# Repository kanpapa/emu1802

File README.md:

# emu1802
The computer with only COSMAC CDP1802 and PIC18F47Q43/PIC18F27Q43  
developed by Kazuhiro Ouchi

The purpose of this experiment is to see if it is possible to make a real COSMAC work with fewer components, at a lower cost, and more compactly.

The EMU1802 is replacement the CPU of the EMUZ80 with a COSMAC.  
The EMU1802-mini is replacement the PIC of the EMU1802 with a PIC18F27Q43.  

## Repository Contents
- [emu1802.X](/emu1802.X/) - PIC18F47Q43 ROM RAM and UART emulation firmware for EMU1802
- [emu1802mini.X](/emu1802mini.X/) - PIC18F27Q43 ROM RAM and UART emulation firmware for EMU1802-mini
- [production](/production/) - Firmware hex files for EMU1802-mini
- [idiotmon](/idiotmon/) - IDIOT/4 monitor and sample programs
- [kicad/emu1802_sch.pdf](/kicad/emu1802_sch.pdf) - schematic of EMU1802
- [kicad/emu1802_mini_sch.pdf](/kicad/emu1802_mini_sch.pdf) - schematic of EMU1802-mini
- [kicad/emu1802_mini_bom.md](/kicad/emu1802_mini_bom.md) - BOM of EMU1802-mini
- [test_programs](/test_programs/) - Test programs for EMU1802 hardware
- [tools/bin2hexsrc.py](/tools/bin2hexsrc.py) - A tool to convert binaries to HEX
- [EMU1802mini_Setup_ja.md](/EMU1802mini_Setup_ja.md) - Setup manual for EMU1802mini (Japanese)
- [README.md](/README.md) - This manual

## Development tools
- [Microchip MPLAB IDE v6.00](https://www.microchip.com/en-us/tools-resources/develop/mplab-x-ide)
- [Microchip MPLAB SNAP](https://www.microchip.com/en-us/development-tool/PG164100)
- [SB-Assembler 3](https://www.sbprojects.net/sbasm/)
- Python3

## Blog
You can also refer to my blog. (in Japanese)  
https://kanpapa.com/cosmac/blog/emu1802/

## Pictures

The EMU1802-mini  

Testing of the EMU1802-mini  

The idiot monitor is working on the EMU1802-mini  

Prototype of The EMU1802  

## License Information
References to any products, programs or services do not imply that they will be available in all countries in which their respective owner operates.  

Company, product, or services names may be trademarks or services marks of others.  

All libraries used in this code are copyright their respective authors.  

This project is based on the EMUZ80 hardware and software developed by Tetsuya Suzuki.

EMUZ80 - The computer with only Z80 and PIC18F47Q43  
  Written by Tetsuya Suzuki  
  https://github.com/vintagechips/emuz80  

The firmware includes the IDIOT monitor.  

IDIOT/4 MONITOR FOR THE 1802  
  WRITTEN: 6/23/82 BY LEE HART  
  COPYRIGHT 1982-85 BY TMSI  
  This program may be used for any noncommercial use free of charge.  
  fixes by Herb Johnson HRJ April 2010, Jan 2014  
  https://www.retrotechnology.com/memship/mship_idiot.html

Thanks to Gazelle for optimizing the firmware.  

  Modified by Gazelle  
  https://drive.google.com/drive/folders/14-OX5THzVz1BVxLPXheExVnpIBqS79NJ  
  1st release 2022-7-29

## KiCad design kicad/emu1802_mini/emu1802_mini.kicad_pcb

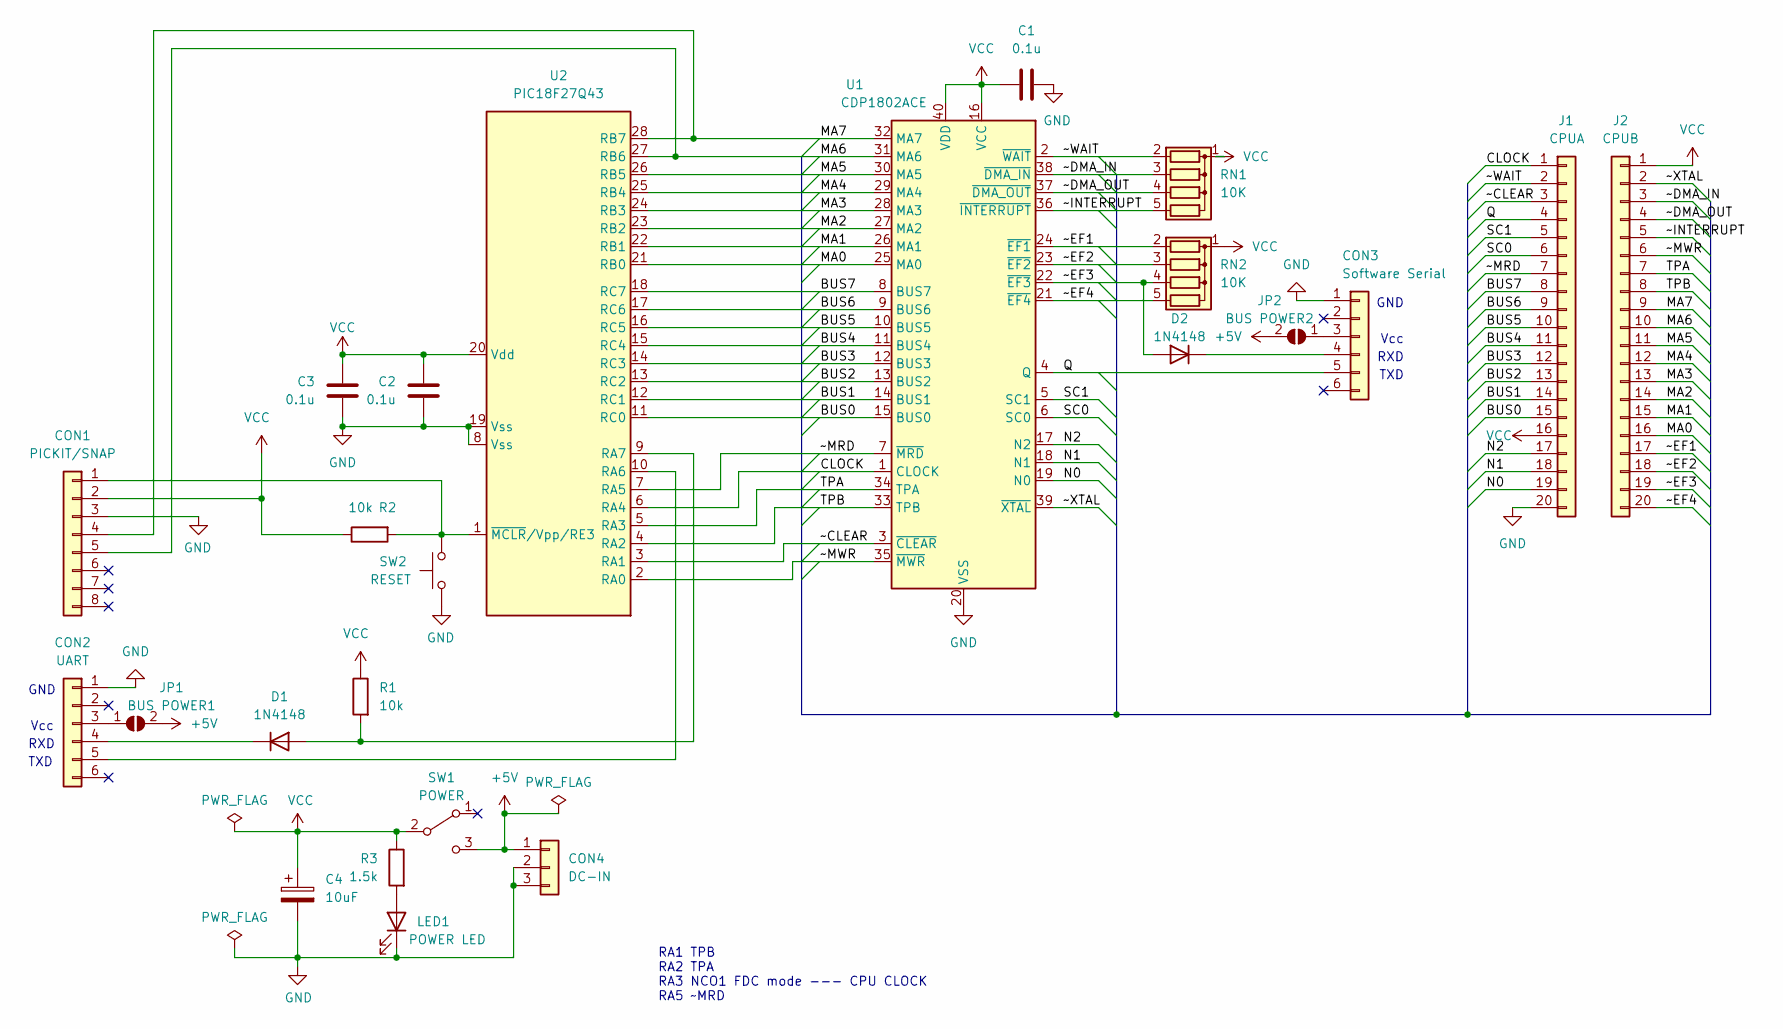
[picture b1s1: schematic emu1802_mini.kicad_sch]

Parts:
C1, C2, C3: 0.1u; C_Disc_D3.0mm_W1.6mm_P2.50mm
C4: 10uF; CP_Radial_D4.0mm_P2.00mm
CON1: PICKIT/SNAP; PinHeader_1x08_P2.54mm_Vertical
CON2: UART; PinHeader_1x06_P2.54mm_Vertical
CON3: Software Serial; PinHeader_1x06_P2.54mm_Vertical
CON4: DC-IN; PinHeader_1x03_P2.54mm_Vertical
D1, D2: 1N4148; D_T-1_P5.08mm_Horizontal
J1: CPUA; PinSocket_1x20_P2.54mm_Vertical
J2: CPUB; PinSocket_1x20_P2.54mm_Vertical
JP1: BUS POWER1; SolderJumper-2_P1.3mm_Open_RoundedPad1.0x1.5mm
JP2: BUS POWER2; SolderJumper-2_P1.3mm_Open_RoundedPad1.0x1.5mm
LED1: POWER LED; LED_D3.0mm
R1, R2: 10k; R_Axial_DIN0204_L3.6mm_D1.6mm_P5.08mm_Horizontal
R3: 1.5k; R_Axial_DIN0204_L3.6mm_D1.6mm_P5.08mm_Horizontal
RN1, RN2: 10K; R_Array_SIP5
SW1: POWER; PinHeader_1x03_P2.54mm_Vertical
SW2: RESET; SW_PUSH_6mm
U1: CDP1802ACE; DIP-40_W15.24mm_Socket
U2: PIC18F27Q43; DIP-28_W7.62mm_Socket

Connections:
+5V: CON4.1, JP1.2 (B), JP2.2 (B), SW1.3 (C)
/BUS0: J1.15, U1.15 (BUS0), U2.11 (RC0)
/BUS1: J1.14, U1.14 (BUS1), U2.12 (RC1)
/BUS2: J1.13, U1.13 (BUS2), U2.13 (RC2)
/BUS3: J1.12, U1.12 (BUS3), U2.14 (RC3)
/BUS4: J1.11, U1.11 (BUS4), U2.15 (RC4)
/BUS5: J1.10, U1.10 (BUS5), U2.16 (RC5)
/BUS6: J1.9, U1.9 (BUS6), U2.17 (RC6)
/BUS7: J1.8, U1.8 (BUS7), U2.18 (RC7)
/CLOCK: J1.1, U1.1 (CLOCK), U2.6 (RA4)
/MA0: J2.16, U1.25 (MA0), U2.21 (RB0)
/MA1: J2.15, U1.26 (MA1), U2.22 (RB1)
/MA2: J2.14, U1.27 (MA2), U2.23 (RB2)
/MA3: J2.13, U1.28 (MA3), U2.24 (RB3)
/MA4: J2.12, U1.29 (MA4), U2.25 (RB4)
/MA5: J2.11, U1.30 (MA5), U2.26 (RB5)
/MA6: CON1.5, J2.10, U1.31 (MA6), U2.27 (RB6)
/MA7: CON1.4, J2.9, U1.32 (MA7), U2.28 (RB7)
/N0: J1.19, U1.19 (N0)
/N1: J1.18, U1.18 (N1)
/N2: J1.17, U1.17 (N2)
/Q: CON3.5, J1.4, U1.4 (Q)
/SC0: J1.6, U1.6 (SC0)
/SC1: J1.5, U1.5 (SC1)
/TPA: J2.7, U1.34 (TPA), U2.5 (RA3)
/TPB: J2.8, U1.33 (TPB), U2.4 (RA2)
/~CLEAR: J1.3, U1.3 (~CLEAR), U2.3 (RA1)
/~DMA_IN: J2.3, RN1.3 (R2), U1.38 (~DMA_IN)
/~DMA_OUT: J2.4, RN1.4 (R3), U1.37 (~DMA_OUT)
/~EF1: J2.17, RN2.2 (R1), U1.24 (~EF1)
/~EF2: J2.18, RN2.3 (R2), U1.23 (~EF2)
/~EF3: D2.2 (A), J2.19, RN2.4 (R3), U1.22 (~EF3)
/~EF4: J2.20, RN2.5 (R4), U1.21 (~EF4)
/~INTERRUPT: J2.5, RN1.5 (R4), U1.36 (~INTERRUPT)
/~MRD: J1.7, U1.7 (~MRD), U2.7 (RA5)
/~MWR: J2.6, U1.35 (~MWR), U2.2 (RA0)
/~WAIT: J1.2, RN1.2 (R1), U1.2 (~WAIT)
/~XTAL: J2.2, U1.39 (~XTAL)
GND: C1.1, C2.2, C3.2, C4.2, CON1.3, CON2.1, CON3.1, CON4.2, CON4.3, J1.20, LED1.1 (K), SW2.2, U1.20 (VSS), U2.8 (Vss), U2.19 (Vss)
unnamed: CON1.1, R2.2, SW2.1, U2.1 (~MCLR/Vpp/RE3)
unnamed: CON2.3, JP1.1 (A)
unnamed: CON2.4, D1.1 (K)
unnamed: CON2.5, U2.10 (RA6)
unnamed: CON3.3, JP2.1 (A)
unnamed: CON3.4, D2.1 (K)
unnamed: D1.2 (A), R1.2, U2.9 (RA7)
unnamed: LED1.2 (A), R3.2
VCC: C1.2, C2.1, C3.1, C4.1, CON1.2, J1.16, J2.1, R1.1, R2.1, R3.1, RN1.1 (common), RN2.1 (common), SW1.2 (B), U1.16 (VCC), U1.40 (VDD), U2.20 (Vdd)

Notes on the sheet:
RXD
TXD
GND
Vcc
RA1 TPB RA2 TPA RA3 NCO1 FDC mode --- CPU CLOCK RA5 ~MRD

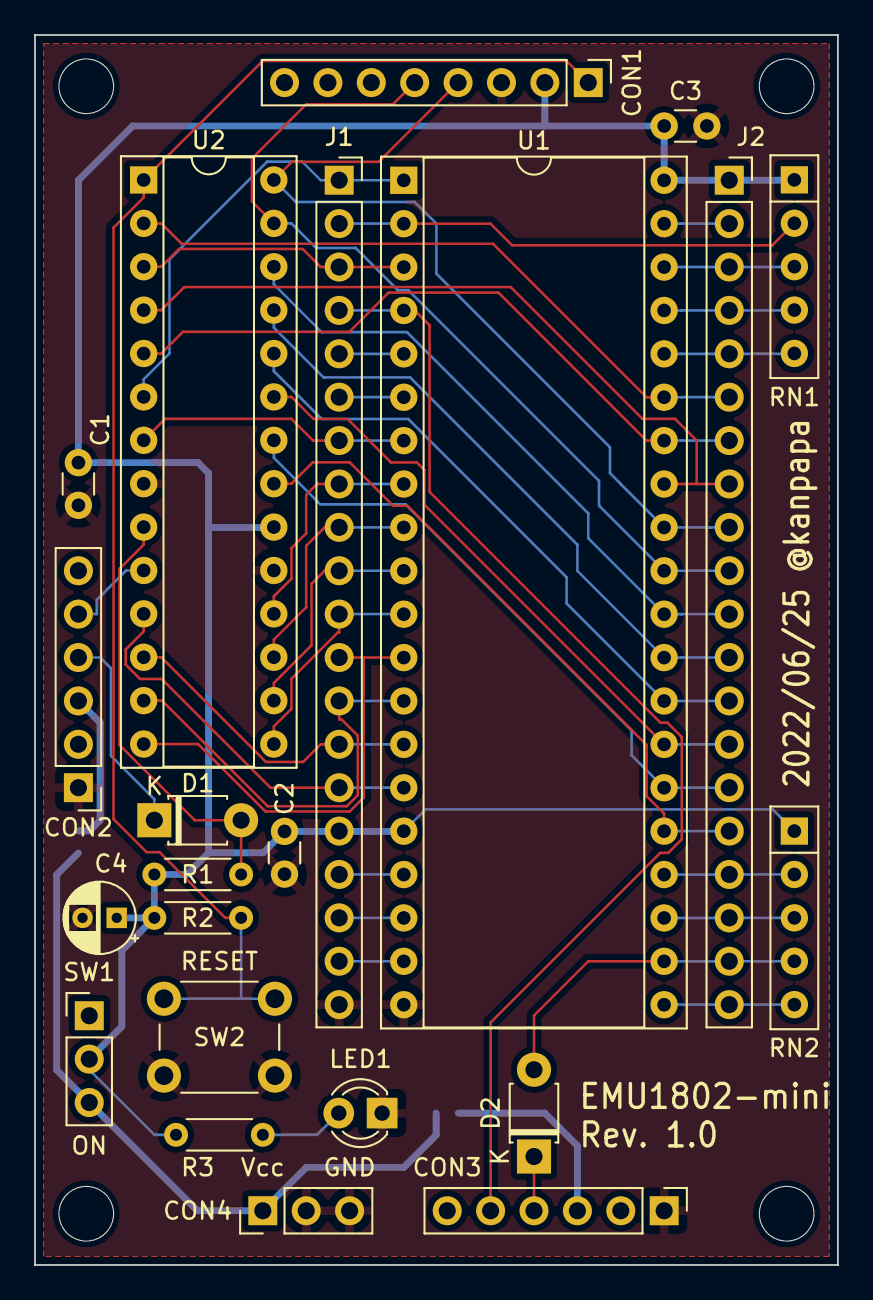
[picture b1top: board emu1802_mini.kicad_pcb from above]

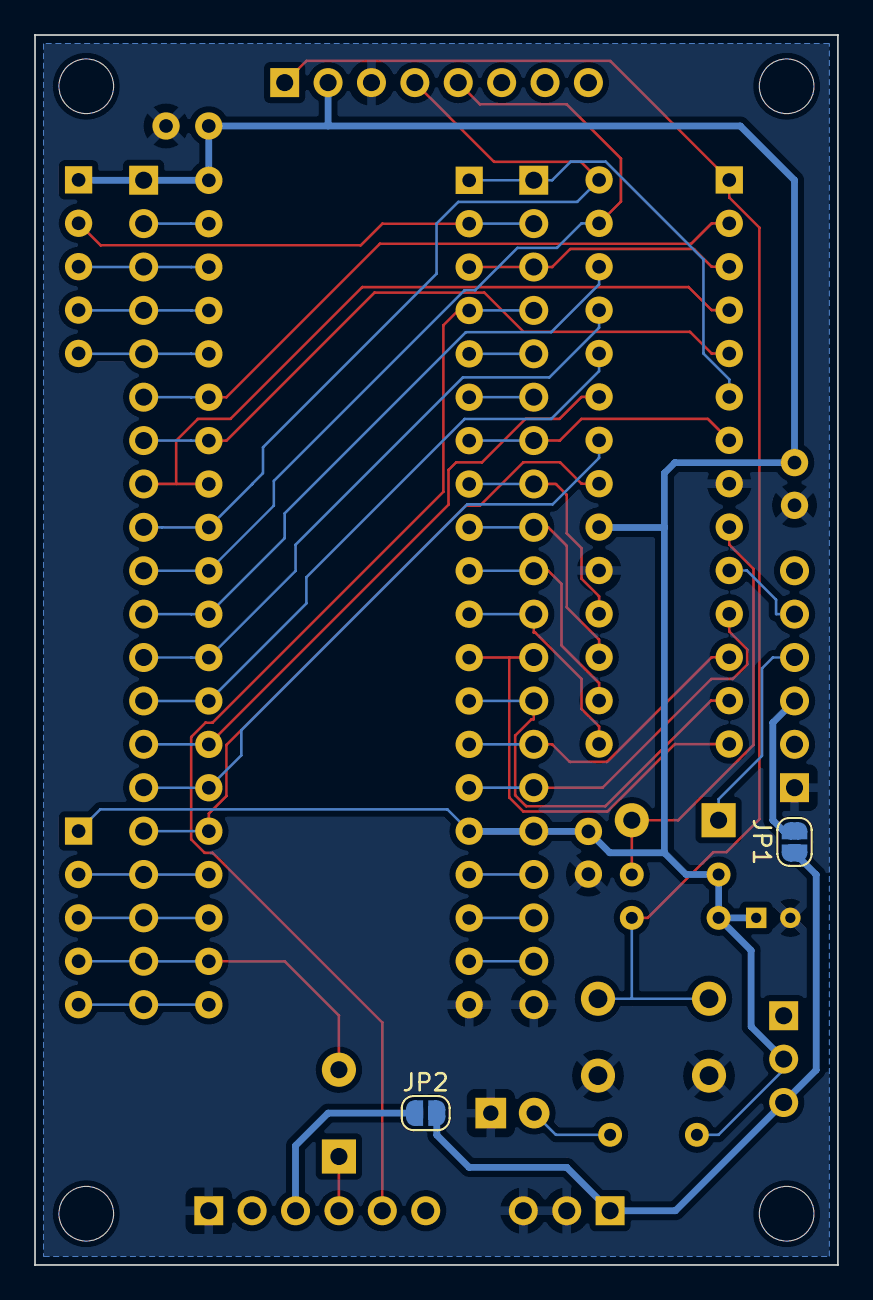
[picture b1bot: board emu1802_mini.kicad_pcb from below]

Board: 2 copper layers, 47.0 x 72.0 mm, 28 parts (2 on the bottom side), 48 nets.

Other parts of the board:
MH1, MH2, MH3, MH4: MountingHole_3.2mm_M3

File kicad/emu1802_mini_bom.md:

# EMU1802-mini Rev1.0 BOM
|Item|Qty|Reference(s)|Value|Description|Datasheet|
| --- | --- | --- | --- | --- | --- |
|1|3|C1, C2, C3|0.1u|Leaded MLCC 0.1uF50V 2.54mm|https://akizukidenshi.com/catalog/g/gP-00090/|
|2|1|C4|10uF|capacitor 10uF50V|https://akizukidenshi.com/catalog/g/gP-03116/|
|3|1|CON1|PICKIT/SNAP|2.54mm 8-Pin header strip straight(or right angle) single row|https://akizukidenshi.com/catalog/g/gC-00167/|
|4|1|CON2|UART|2.54mm 6-Pin header strip straight(or right angle) single row|https://akizukidenshi.com/catalog/g/gC-00167/|
|5|1|CON3|Software Serial|2.54mm 6-Pin header strip straight(or right angle) single row|https://akizukidenshi.com/catalog/g/gC-00167/|
|6|1|CON4|DC-IN|2.54mm 3-Pin header strip straight(or right angle) single row|https://akizukidenshi.com/catalog/g/gC-00167/|
|7|2|D1, D2|1N4148| Small Signal Diode 1N4148|https://akizukidenshi.com/catalog/g/gI-00941/|
|8|2|J1, J2|CPUA/B|2.54mm 20-Pin female header single row straight dip|https://akizukidenshi.com/catalog/g/gC-03077/|
|9|1|LED1|POWER LED|3mm LED|https://akizukidenshi.com/catalog/g/gI-11577/|
|10|2|R1, R2|10k|resistor 10k 1/6W|https://akizukidenshi.com/catalog/g/gR-16103/|
|11|1|R3|1.5k|resistor 1.5k 1/6W|https://akizukidenshi.com/catalog/g/gR-16152/|
|12|2|RN1,RN2|10K|SIP resistor 5-pin 4 x 10k|https://akizukidenshi.com/catalog/g/gR-11909/|
|13|1|SW1|POWER|slide switch SS-12D00G3|https://akizukidenshi.com/catalog/g/gP-15707/|
|14|1|SW2|RESET|tact switch TS-0606|https://akizukidenshi.com/catalog/g/gP-03649/|
|15|1|U1|CDP1802ACE|CDP1802ACE microprocessor|http://www.cosmacelf.com/publications/data-sheets/cdp1802.pdf|
|16|1|U2|PIC18F27Q43|Microchip PIC18F27Q43 microprocessor|https://akizukidenshi.com/catalog/g/gI-16593/|
|17|1|U1 socket||40-Pin IC socket 600mil |https://akizukidenshi.com/catalog/g/gP-00034/|
|18|1|U2 socket||28-Pin IC socket 300mil|https://akizukidenshi.com/catalog/g/gP-01339/|

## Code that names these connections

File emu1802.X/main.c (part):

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#pragma config FCMEN = ON       // Fail-Safe Clock Monitor Enable bit (Fail-Safe Clock Monitor enabled)

// CONFIG3
#pragma config MCLRE = EXTMCLR  // MCLR Enable bit (If LVP = 0, MCLR pin is MCLR; If LVP = 1, RE3 pin function is MCLR )
#pragma config PWRTS = PWRT_OFF // Power-up timer selection bits (PWRT is disabled)
#pragma config MVECEN = ON      // Multi-vector enable bit (Multi-vector enabled, Vector table used for interrupts)
#pragma config IVT1WAY = ON     // IVTLOCK bit One-way set enable bit (IVTLOCKED bit can be cleared and set only once)
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    address.h = PORTB;  // Read address high
}

void __interrupt(irq(IOC),base(8)) PIN_MANAGER_IOC()
{   
	// interrupt on change for pin IOCAF1
    if(IOCAFbits.IOCAF1 == 1)
    {
        IOCAF1_ISR();  
    }	
	// interrupt on change for pin IOCAF2
    if(IOCAFbits.IOCAF2 == 1)
    {
        IOCAF2_ISR();  
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
// Called at COSMAC TPB falling edge (PIC18F47Q43 issues WAIT)
void __interrupt(irq(CLC1),base(8)) CLC1_ISR(){
    CLC1IF = 0; // Clear interrupt flag
    
    //address.h = 0; // Read address high (256byte only)
    address.l = PORTB; // Read address low
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// Called at COSMAC TPA falling edge (PIC18F47Q43 issues WAIT)
void __interrupt(irq(CLC2),base(8)) CLC2_ISR()
{
    CLC2IF = 0;         // Clear the CLC interrupt flag
    address.h = PORTB;  // Read address high
}

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
//  Called at COSMAC TPB(RA1) Falling edge
void __interrupt(irq(INT0),base(8)) INT0_ISR(){
    INT0IF = 0; // Clear interrupt flag
    db_setin(); // Set data bus as input
}

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    WPUD = 0xff; // Week pull up
    TRISD = 0xff; // Set as input

    // Address bus A7-A0 pin (RB0-RB7)
    ANSELB = 0x00; // Disable analog function
    WPUB = 0xff; // Week pull up
    TRISB = 0xff; // Set as input

    // Data bus D7-D0 pin (RC0-RC7)
    ANSELC = 0x00; // Disable analog function
    WPUC = 0xff; // Week pull up
    TRISC = 0xff; // Set as input(default)

    // MWR input pin (RE0)
    ANSELE0 = 0; // Disable analog function
    WPUE0 = 1; // Week pull up
    TRISE0 = 1; // Set as input
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
    // INT output pin (RE2) --- Unused
    //ANSELE2 = 0; // Disable analog function
    //LATE2 = 1; // No interrupt request
    //TRISE2 = 0; // Set as output

    // MRD input pin (RA5)
    ANSELA5 = 0; // Disable analog function
    WPUA5 = 1; // Week pull up
    TRISA5 = 1; // Set as intput
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    //U3ON = 1; // Serial port enable
    
    
    // TPB(RA1) CLC1 input pin
    ANSELA1 = 0; // Disable analog function
    WPUA1 = 1; // Week pull up
    TRISA1 = 1; // Set as input
    //CLCIN0PPS = 0x1; //RA1->CLC1:CLCIN0;

    // TPA(RA2) CLC2 input pin
    ANSELA2 = 0; // Disable analog function
    WPUA2 = 1; // Week pull up
    TRISA2 = 1; // Set as input
    //CLCIN1PPS = 0x2; //RA2->CLC1:CLCIN1;

    // RA4 CLC1 output pin --- debug
    //ANSELA4 = 0; // Disable analog function
    //LATA4 = 1; // Default level
    //TRISA4 = 0; // Set as output
    //RA4PPS = 0x01;  //RA4->CLC1:CLC1;

    // RA0 CLC2 output pin --- debug   
    //ANSELA0 = 0; // Disable analog function
    //LATA0 = 1; // Default level
    //TRISA0 = 0; // Set as output
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
    // CLC data inputs select
    CLCnSEL0 = 0x2a;  // D-FF CLK assign NC01
    CLCnSEL1 = 0; // D-FF D assign CLCIN0PPS(RA1) 
    CLCnSEL2 = 127; // D-FF S assign none
    CLCnSEL3 = 127; // D-FF R assign none

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    // INTERRUPT_Initialize
    //
    // Vectored Interrupt Controller setting sequence
    INTCON0bits.IPEN = 1; // Interrupt priority enable

    IVTLOCK = 0x55;
    IVTLOCK = 0xAA;
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
#ifdef false
    // CLC VI enable
    CLC1IF = 0; // Clear the CLC interrupt flag
    CLC1IE = 1; // Enabling CLC1 interrupt
    
    // Assign peripheral interrupt priority vectors
    IPR6bits.CLC2IP = 1;
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    CLCDATA = 0x00;     // CLC2OUT 0; 
    CLCnCON = 0x8C;     // EN enabled; INTN enabled; INTP disabled; MODE 1-input D flip-flop with S and R;

    CLC2IF = 0; // Clear the CLC interrupt flag
    CLC2IE = 1; // Enabling CLC2 interrupt.

#endif

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    INT0IE = 1;
   
    // COSMAC start
    GIE = 1; // Global interrupt enable
    LATE1 = 1; // Release reset COSMAC ~CLEAR(RE1)
    
    while(1); // All things come to those who wait
}
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
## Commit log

2022-06-05 1st commit
2022-06-05 Added schematic of EMU1802.
2022-06-05 Fixed CON2 and CON3
2022-06-05 Added sample programs for IDIOT monitor
2022-06-19 Added EMU1802-mini Schematic
2022-06-19 Added emu1802mini Project
2022-06-20 Added BOM for EMU1802-mini
2022-06-20 Updated BOM
2022-06-22 Added IDIOT/4 Monitor
2022-06-22 Added test programs
2022-06-22 Added setup manual for EMU1802mini
2022-06-22 Updated setup manual
2022-06-22 Added Basic commands for IDIOT monitor
2022-06-23 Added command example for IDIOT monitor
2022-06-23 Added KiCad 6.0 files
2022-06-24 Updated Schematic Rev. 1.0
2022-06-25 Updated BOM Rev. 1.0
2022-07-02 Added how to run BASIC.
2022-07-02 Fixed typo
2022-07-03 Updated main.c for V1.1
2022-07-03 Added echoback for uart
2022-07-04 Added HelloWorld and Echo back for PIC UART
2022-07-05 Update setup manual
2022-07-05 Added uart sample program for idiot monitor
2022-07-06 Added idiot_uart
2022-07-09 Bugfix IDIOT Using UART of PIC
2022-07-09 Added Tips
2022-07-09 Added comments
2022-07-10 Updated documents
2022-07-12 Updated emu1802-mini PCB Rev.1.0
2022-07-12 Added pictures
2022-07-12 moved pictures
2022-07-13 Added EMU1802 archive
2022-07-14 Update documents
2022-07-17 Added hex files
2022-07-17 Added readme
2022-07-17 Renamed folder
2022-07-30 Updated firmware V2.1G
2022-07-30 Added V2.1G
2022-07-30 Updated setup manual for V2.1G
2022-07-30 Fixed setup manual
2022-07-30 Added asciiart.bas
2022-07-30 Fixed markdown syntax
2022-07-31 Fixed bugs
